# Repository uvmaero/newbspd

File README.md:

# BSPD
Documentation and design file related to BSPD system development.

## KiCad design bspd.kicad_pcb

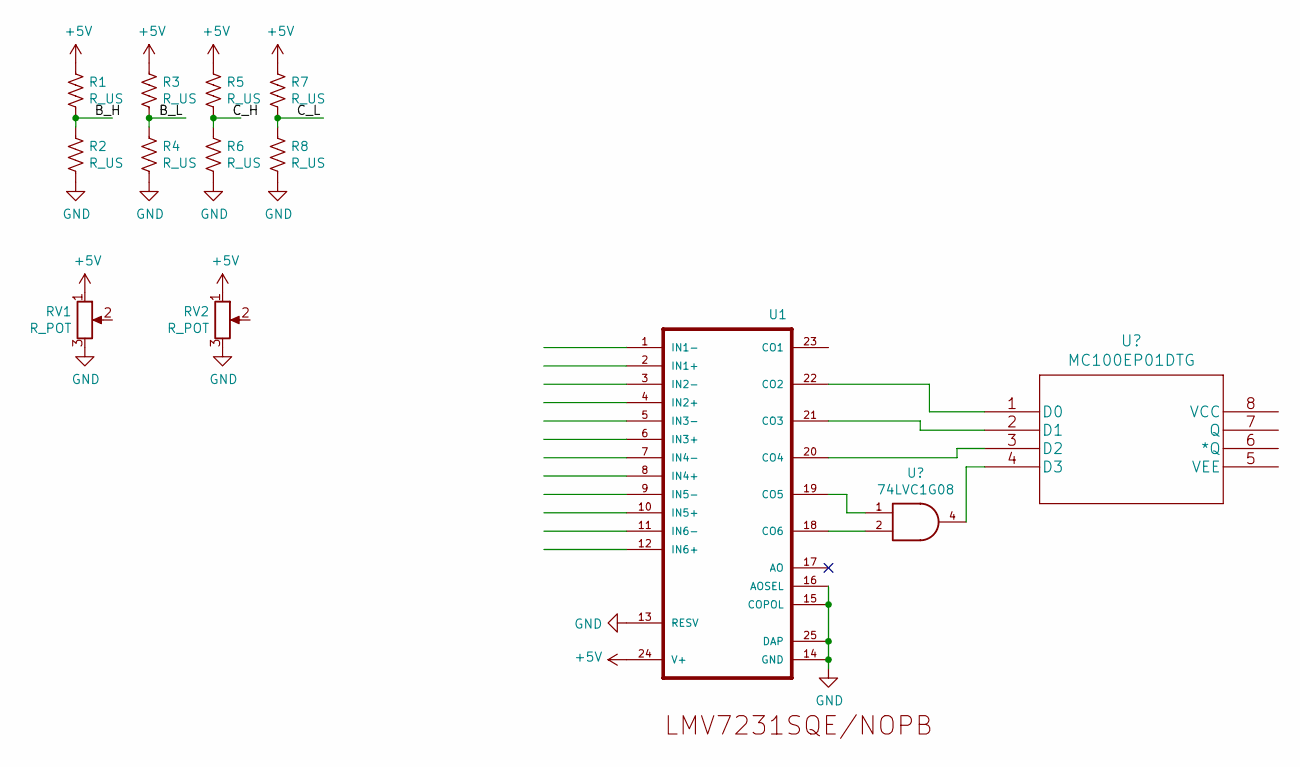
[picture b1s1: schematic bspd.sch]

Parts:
R1, R2, R3, R4, R5, R6, R7, R8: R_US; R_0603_1608Metric
RV1, RV2: R_POT; 3339H-1-103LF
U1: TI_NATIONAL_SEMICONDUCTOR_LMV7231SQE-NOPB; TI_NATIONAL_SEMICONDUCTOR_LMV7231SQE-NOPB_0

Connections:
+5V: R1.1, R3.1, R5.1, R7.1, RV1.1, RV2.1, U1.24 (V+)
/B_H: R1.2, R2.1
/B_L: R3.2, R4.1
/C_H: R5.2, R6.1
/C_L: R7.2, R8.1
GND: R2.2, R4.2, R6.2, R8.2, RV1.3, RV2.3, U1.13 (RESV), U1.14 (GND), U1.15 (COPOL), U1.16 (AOSEL), U1.25 (DAP)

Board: 2 copper layers, 11 parts (0 on the bottom side), 6 nets, no tracks yet.

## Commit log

2019-12-16 Start kicad
2019-12-18 fix or gate
